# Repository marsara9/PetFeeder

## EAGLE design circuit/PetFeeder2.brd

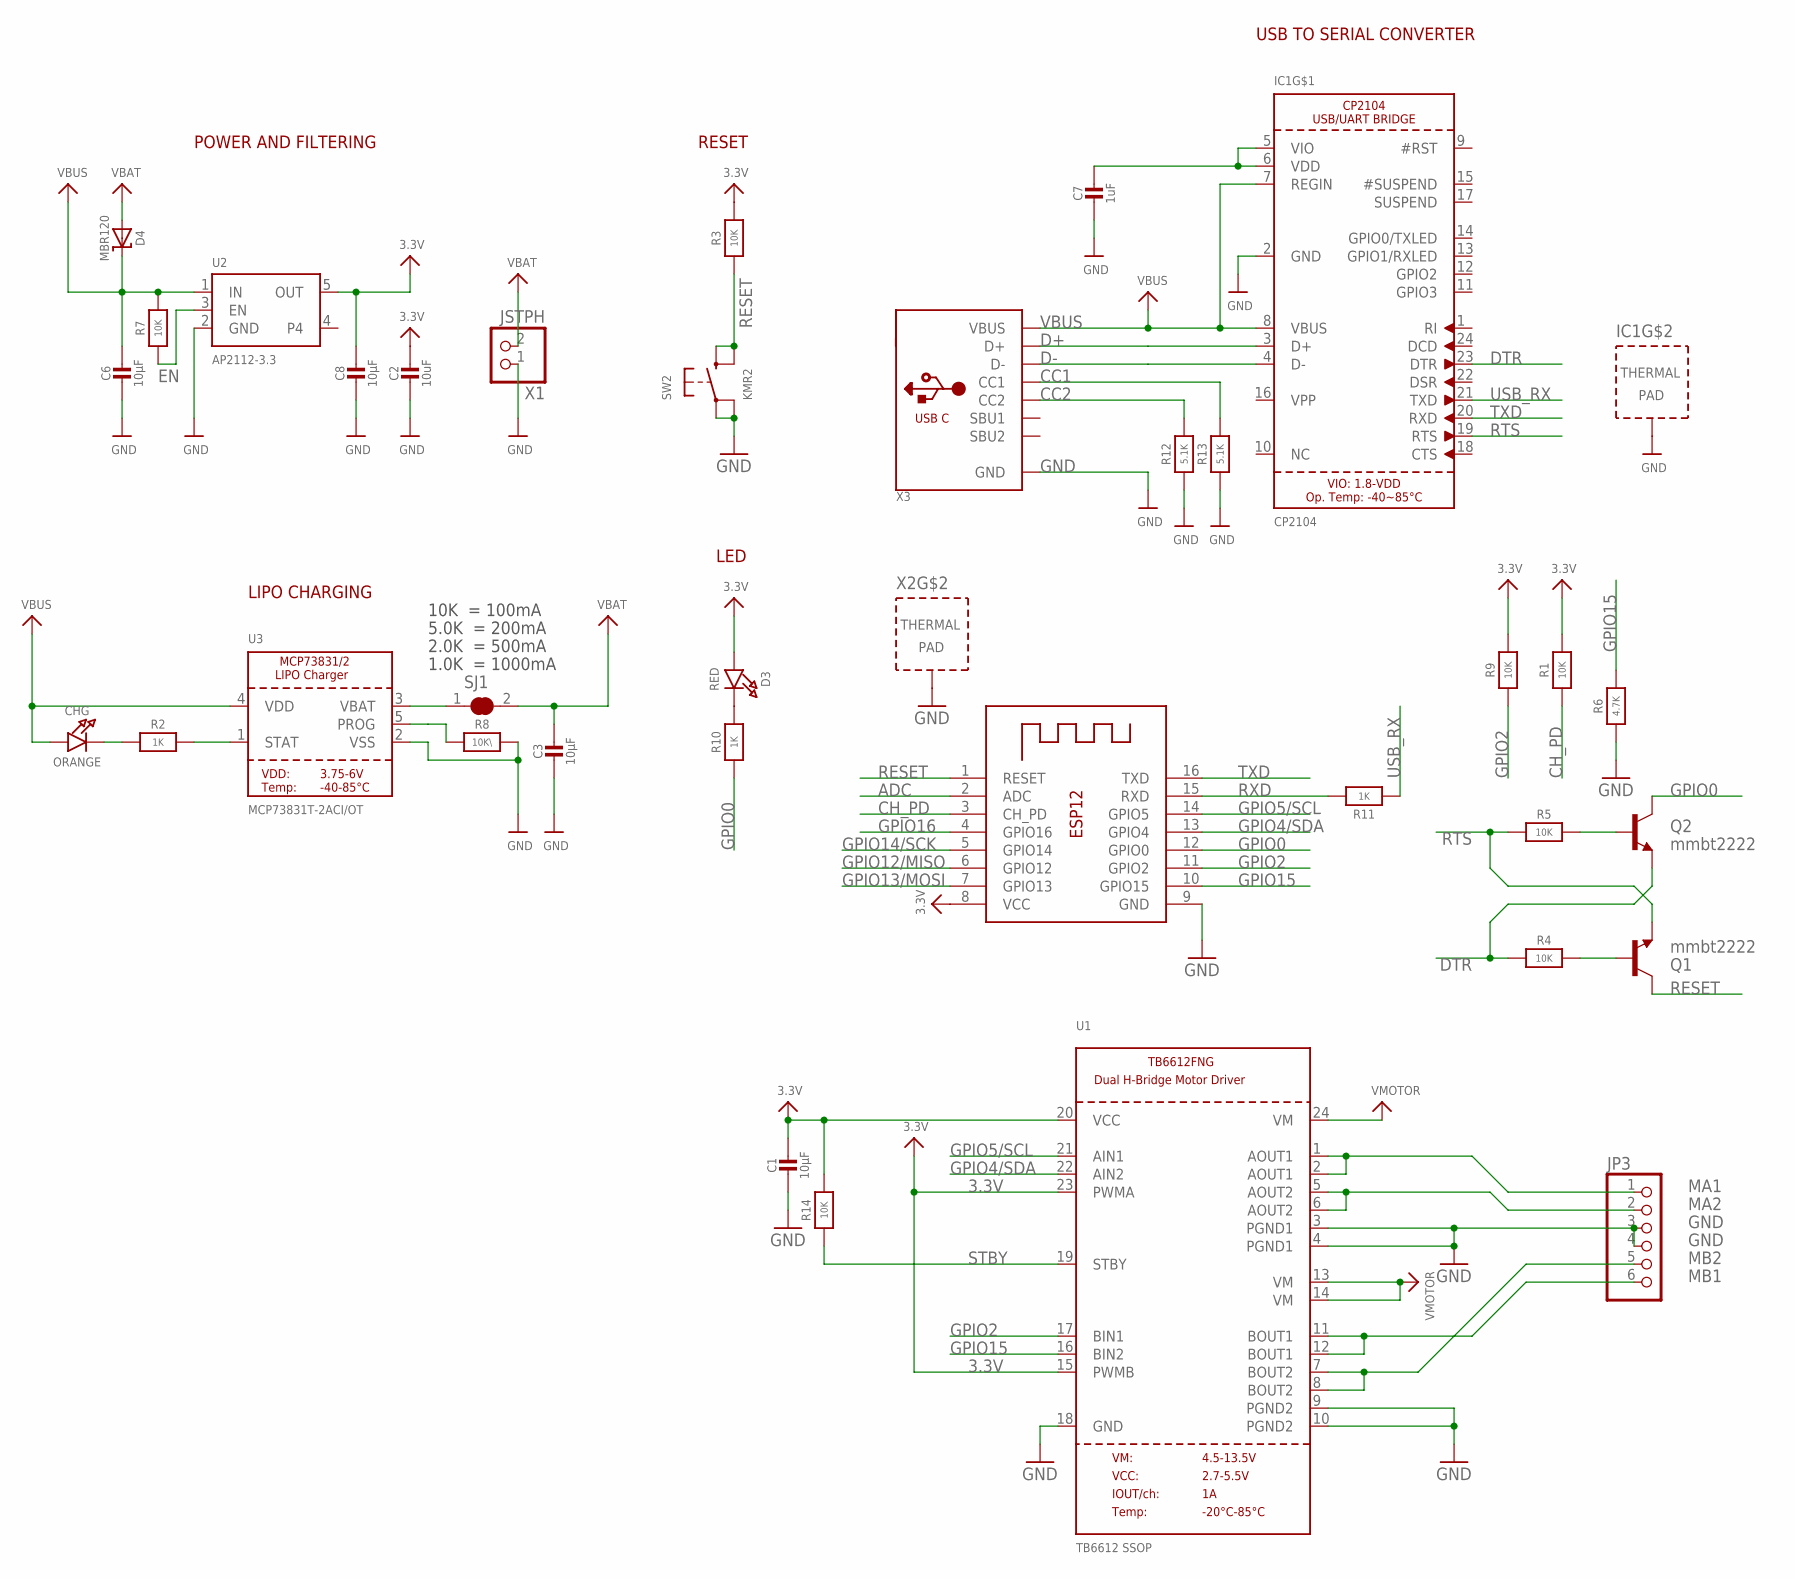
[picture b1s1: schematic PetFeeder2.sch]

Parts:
C1, C3, C6, C8: 10µF; 0805-NO
C2: 10uF; 0805-NO
C7: 1uF; 0603-NO
CHG: ORANGE; CHIPLED_0805_NOOUTLINE
D3: RED; CHIPLED_0805_NOOUTLINE
D4: MBR120; SOD-123
IC1: CP2104; QFN24_4MM_SMSC
JP3: PINHD-1X6CB; 1X06-CLEANBIG
Q1, Q2: mmbt2222; SOT23-3
R1, R3, R4, R5, R7, R9: 10K; 0603-NO
R2, R10: 1K; 0603-NO
R6: 4.7K; 0603-NO
R8: 10K\; 0603-NO
R11: 1K; _0603MP
R12, R13: 5.1K; 0603-NO
R14: 10K; 0805-NO
SJ1: SOLDERJUMPER_CLOSED; SOLDERJUMPER_CLOSEDWIRE
SW2: KMR2; BTN_KMR2_4.6X2.8
U1: TB6612 SSOP; SSOP24
U2: AP2112-3.3; SOT23-5
U3: MCP73831T-2ACI/OT; SOT23-5
X1: JSTPH; JSTPH2
X2: ESP-12; ESP-12S
X3: USB_C; USB_C_CUSB31-CFM2AX-01-X

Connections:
3.3V: C1.1, C2.1, C8.1, D3.A, R1.2, R3.2, R9.2, R14.2, U1.15 (PWMB), U1.20 (VCC), U1.23 (PWMA), U2.5 (OUT), X2.8 (VCC)
ADC: X2.2 (ADC)
CC1: R13.2, X3.A5 (CC1)
CC2: R12.2, X3.B5 (CC2)
CH_PD: R1.1, X2.3 (CH_PD)
D+: IC1.3 (D+), X3.A6 (D+), X3.B6 (D+)
D-: IC1.4 (D-), X3.A7 (D-), X3.B7 (D-)
DTR: IC1.23 (DTR), Q2.2 (E), R4.1
EN: R7.1, U2.3 (EN)
GND: C1.2, C2.2, C3.2, C6.2, C7.2, C8.2, IC1.2 (GND), IC1.THERM (TP), JP3.3, JP3.4, R6.1, R8.2, R12.1, R13.1, SW2.A, SW2.A' (P1), U1.3 (PGND1), U1.4 (PGND1), U1.9 (PGND2), U1.10 (PGND2), U1.18 (GND), U2.2 (GND), U3.2 (VSS), X1.1, X2.9 (GND), X2.P$1 (TP), X3.A1B12 (GND), X3.B1A12 (GND)
GPIO0: Q2.3 (C), R10.1, X2.12 (GPIO0)
GPIO2: R9.1, U1.17 (BIN1), X2.11 (GPIO2)
GPIO4/SDA: U1.22 (AIN2), X2.13 (GPIO4)
GPIO5/SCL: U1.21 (AIN1), X2.14 (GPIO5)
GPIO12/MISO: X2.6 (GPIO12)
GPIO13/MOSI: X2.7 (GPIO13)
GPIO14/SCK: X2.5 (GPIO14)
GPIO15: R6.2, U1.16 (BIN2), X2.10 (GPIO15)
GPIO16: X2.4 (GPIO16)
MA1: JP3.1, U1.1 (AOUT1), U1.2 (AOUT1)
MA2: JP3.2, U1.5 (AOUT2), U1.6 (AOUT2)
MB1: JP3.6, U1.11 (BOUT1), U1.12 (BOUT1)
MB2: JP3.5, U1.7 (BOUT2), U1.8 (BOUT2)
unnamed: CHG.C, R2.1
unnamed: R2.2, U3.1 (STAT)
unnamed: R8.1, U3.5 (PROG)
unnamed: D3.C, R10.2
unnamed: SJ1.1, U3.3 (VBAT)
unnamed: C7.1, IC1.5 (VIO), IC1.6 (VDD)
unnamed: Q1.1 (B), R4.2
unnamed: Q2.1 (B), R5.2
RESET: Q1.3 (C), R3.1, SW2.B (S), SW2.B' (S1), X2.1 (RESET)
RTS: IC1.19 (RTS), Q1.2 (E), R5.1
RXD: R11.2, X2.15 (RXD)
STBY: R14.1, U1.19 (STBY)
TXD: IC1.20 (RXD), X2.16 (TXD)
USB_RX: IC1.21 (TXD), R11.1
VBAT: C3.1, D4.A, SJ1.2, X1.2
VBUS: C6.1, CHG.A, D4.C, IC1.7 (REGIN), IC1.8 (VBUS), R7.2, U2.1 (IN), U3.4 (VDD), X3.A4B9 (VBUS), X3.B4A9 (VBUS)
VMOTOR: U1.13 (VM), U1.14 (VM), U1.24 (VM)

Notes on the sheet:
USB TO SERIAL CONVERTER
RESET
POWER AND FILTERING
10K = 100mA
5.0K = 200mA
2.0K = 500mA
1.0K = 1000mA
LIPO CHARGING
LED

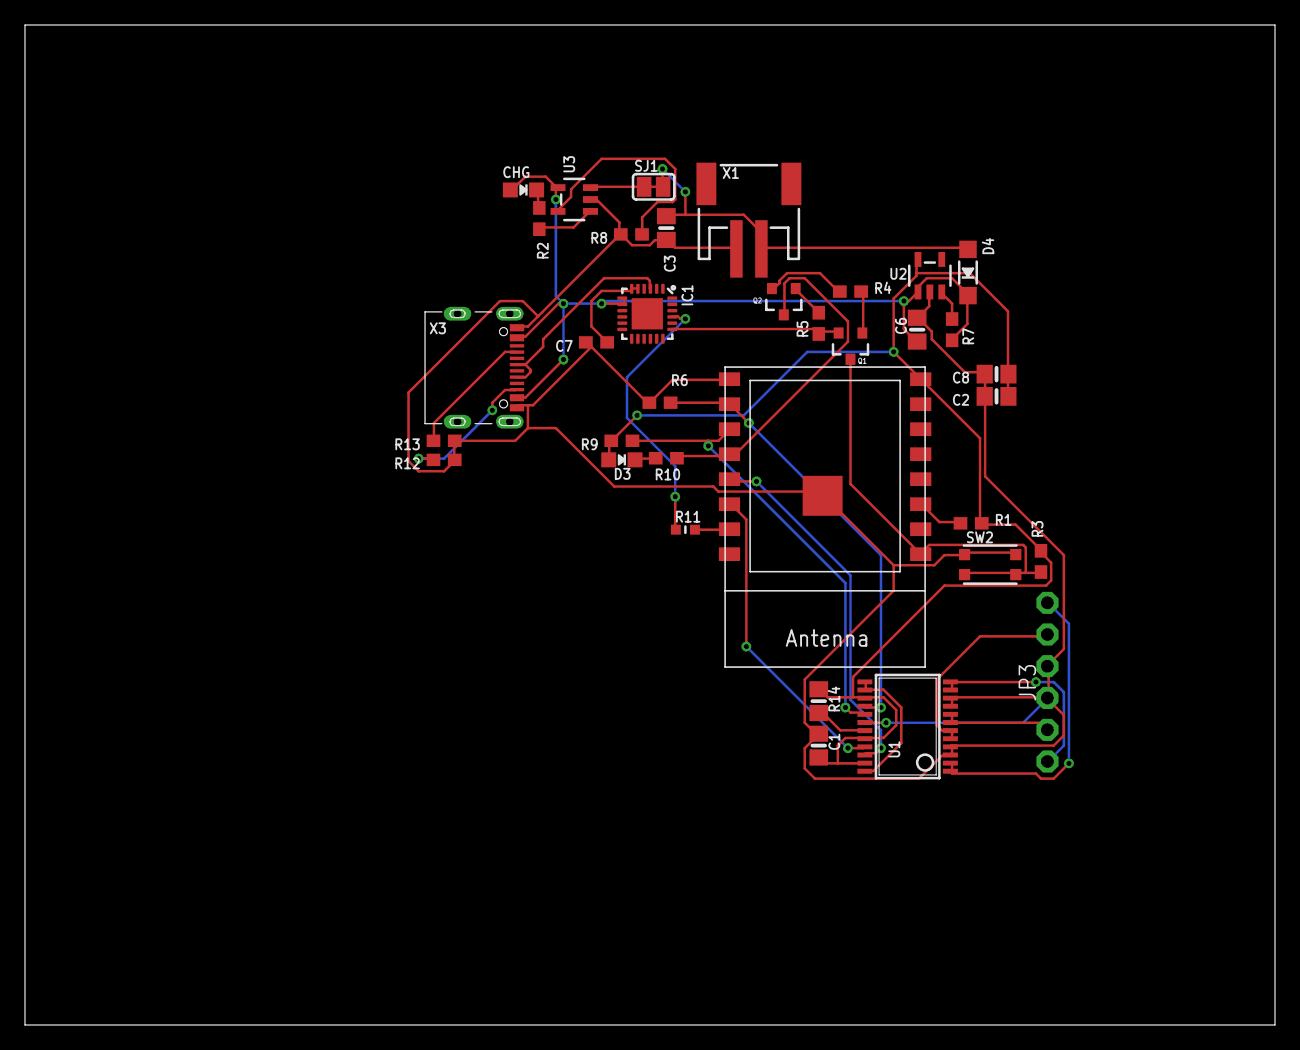
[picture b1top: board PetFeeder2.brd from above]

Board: 2 copper layers, 100.0 x 80.0 mm, 35 parts (0 on the bottom side), 35 nets.

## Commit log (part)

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2020-07-21 adding code to develop
2020-07-21 adding 3d prints and circuit designs
2020-07-21 Adding Postmain API file
2020-07-21 Adding sketchup design.
2020-07-21 adding generic functions for reading and writing raw data to the SD card.
2020-07-21 adding reading/writing Feedings and Schedules
2020-07-21 updating stl files
2020-07-21 fixing memory leak
2020-07-22 renaming ActivityHistory to DataStore; implementing more of the methods.
2020-07-22 updating sketch
2020-07-22 Fixing MDNS
2020-07-22 Removing support to store data in EEPROM if SD card is not available. An SD card is now required. Added support for storing Settings.
2020-07-22 replacing char* with std::string for easier memory management.
2020-07-22 fixed SD card implementaion
2020-07-23 - Fixing memory leaks with DataStore - Fixing issue with mDNS not working - If no name is set, a random name is generated and used instead. This same name is ALWAYS used as the access point name when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
2020-07-25 Fixing issue with stepper motor causing watchdog reset.
2020-07-25 Implementing GET /feed to get all of the feedings.
2020-07-25 fixing headers.
2020-07-25 code cleanup
2020-07-26 Adding scheduler
2020-07-26 Adding GET/POST requests to get or add new scheduled feedings.
2020-07-26 Fixed bug with DataStore::writeBytesToFile Adding logging for any web server requests
2020-07-26 implementing scheduleToJson
2020-07-26 Fixed issue with DataStore crashing Implemented POST / GET `/schedule`.
2020-07-26 fixing bug in time calculation. fixing bug where the feeder would dispense at boot.
2020-07-26 updating postman api
2020-07-26 Implementing DELETE settings to restore factory default settings.
2020-07-27 Initial checkin for Android app.
2020-07-27 Adding ViewModels setting up project structure.
2020-07-27 Adding Retrofit and RxKotlin
2020-07-28 Starting work on settings screen
2020-07-28 Exposing Binding from ViewDataBinding to be used later.
2020-07-28 Continuing work on Settings
2020-07-28 cleaning up imports
2020-07-28 Cleaning up dialogs
2020-07-28 Moving settings module to the settings package
2020-07-28 Adding schedules fragment.
2020-07-28 Adding History service calls and view models.
2020-07-28 Fixing issue with settings not reloading correctly. Adding option to reset to factory defaults.
2020-07-29 Updating launcher icon
2020-07-29 Adding DashboardViewModel
2020-07-29 Adding UUID generator Schedule now works with bytes instead of ints Fixed feeding's JSON to emit 'date' instead of 'time'.
2020-07-29 Dashboard now launches on startup
2020-07-29 Adding FCM libraries.
2020-07-29 Adding HistoryFragment. Code cleanup.
2020-07-29 Adding FCM token to Settings screen
2020-07-29 continuing work on FCM service
2020-07-29 working on notification server implementation on feeder.
2020-07-29 moving android notification logic to its own method
2020-07-30 Fixing notification server.
2020-07-30 the FCM SHA Footprint can now be updated via /settings
2020-07-30 code cleanup.
2020-07-30 updating Android to be able to set the FCM fingerprint via /setttings
2020-07-30 Adding repositories to manager your current feeder.
2020-07-30 standardizing mDNS name to PetFeeder and implementing NSD on Android.
2020-07-30 Fixing memory leak with ViewModels and Rx.
2020-07-31 Adding option to launch setup screen
2020-07-31 Begining work on setup screen.
2020-07-31 Adding service call to delete a scheduled feeding
2020-08-03 Fixing NSD implementation. Starting work on first setup screen.
2020-08-03 continuing to fix mDNS implementation
2020-08-04 Adding build_file_checksums to gitignore
2020-08-04 adding classes to be used for each step along the way.
2020-08-05 Refactoring setup to use Fragments
2020-08-05 Adding new setup fragments.
2020-08-06 continuing work on setup screen.
2020-08-06 more work on setup
2020-08-10 Refactoring Setup once again, Finally got it ths time.
2020-08-12 Working on scanning step for setup.
2020-08-19 updating to ArduinoJson 6
2020-08-20 Adding history fragment layout and hooking up bindings.
2020-08-20 Fixing an issue where the scheduler wasn't adding a new scheduled event correctly after the first one finished.
2020-08-20 Unifiying section header design
2020-08-20 Finally fixed the scheduler.
2020-08-25 Disabling stepper to conserve power when not in use.
2020-08-25 History tab now shows time of feeding.
2020-11-18 refactored actrion bar
2020-11-18 fixed synchronization issue
2020-11-18 update project
2020-11-19 Adding avatar image Fixing sort order of feeders in drop down.
2020-11-19 Sorting history from newest to oldest.
2020-11-19 designing scheduling screen and viewModel.
2020-11-20 adding more icons for time of day when scheduling a feeding.
2020-11-20 updating funnel design to hopefully not get trapped food as much
2020-11-20 Adding Dialog for adding a new scheduled feeding (wip)
2020-11-20 Updating feeder firmware to support esp32.
2020-11-25 Testing material design TimePickerDialog
2020-11-27 Updating add scheduled feeding dialog.
2020-12-02 Updating feeder design to use an auger instead of a turn table.
2020-12-07 update feeder design
2021-11-16 Editing feeder design so that motor screws can be recessed Fixing typo in notifications.h
2022-01-07 Updating libraries to new versions.
2022-01-31 Fixing build issues after upgrading to ArcticFox
2022-05-24 Updating app app to API 32 and support for Android Studio Chipmunk
2022-06-06 cleaning up warnings
2022-06-07 Migrating from RxJava to Kotlin Coroutines.
2022-06-10 Fixing bug with updating StateFlows

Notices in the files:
parts and their libraries:
microbuilder: This work is placed in the public domain, and may be freely used for commercial and non-commercial work with the following conditions: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
SparkFun: Licensing: CC v3.0 Share-Alike You are welcome to use this library for commercial purposes.
